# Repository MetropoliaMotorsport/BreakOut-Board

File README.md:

# BreakOut-Board
New BOB design

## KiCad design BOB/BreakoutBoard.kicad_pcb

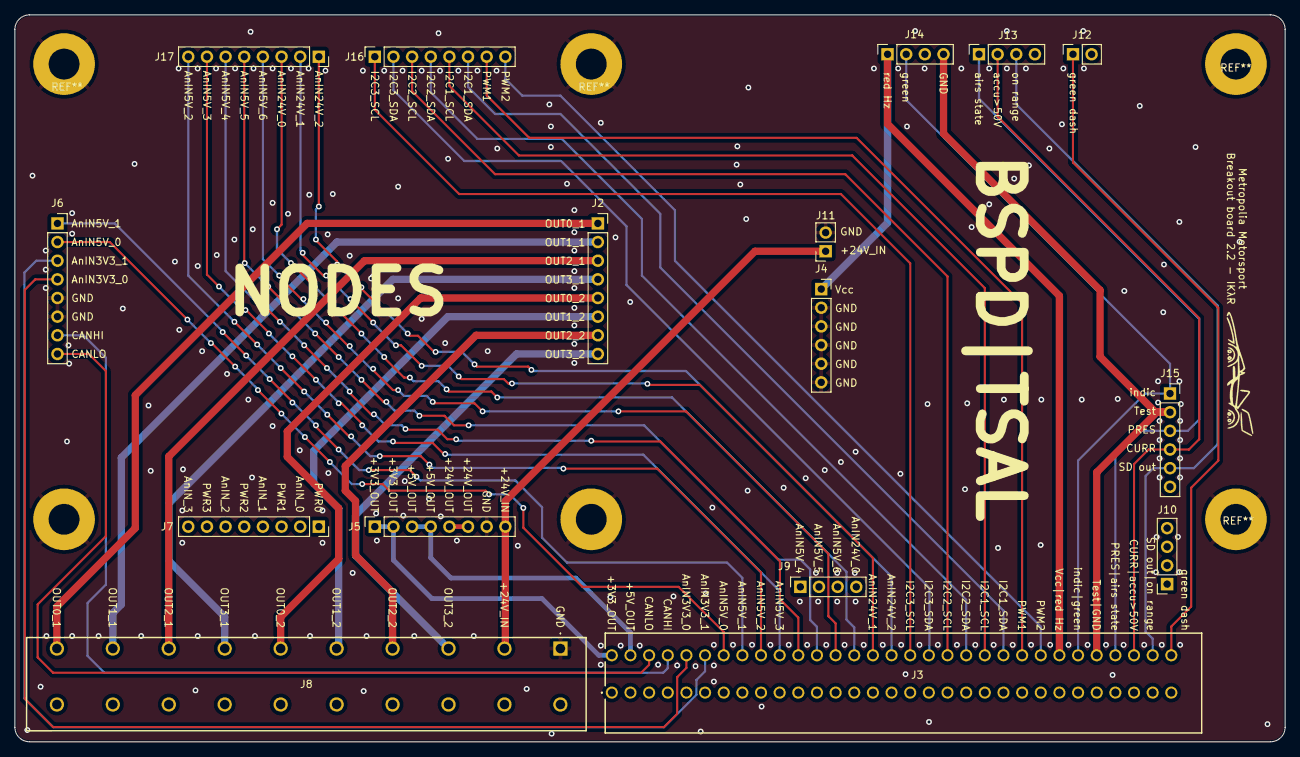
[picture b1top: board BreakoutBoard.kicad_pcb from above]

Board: 2 copper layers, 173.0 x 99.0 mm, 16 parts (0 on the bottom side), 42 nets.

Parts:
J2, J5, J6, J7, J16, J17: Conn_01x08; PinSocket_1x08_P2.54mm_Vertical
J3: 1706013; 35_con_Phoenix
J4, J15: Conn_01x06; PinSocket_1x06_P2.54mm_Vertical
J8: 1700884
J9, J10, J13, J14: Conn_01x04; PinSocket_1x04_P2.54mm_Vertical
J11, J12: Conn_01x02; PinSocket_1x02_P2.54mm_Vertical

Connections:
/+3V3_OUT: J3.2, J5.1, J5.2
/+5V_OUT: J3.4, J5.3, J5.4
/+24V_OUT: J5.5, J5.6
/AnIN3V3_0: J3.10, J6.4
/AnIN3V3_1: J3.12, J6.3
/AnIN5V_0: J3.14, J6.2
/AnIN5V_1: J3.16, J6.1
/AnIN5V_2: J3.18, J17.8
/AnIN5V_3: J3.20, J17.7
/AnIN5V_4: J3.22, J17.6
/AnIN5V_5: J3.24, J17.5
/AnIN5V_6: J3.26, J17.4
/AnIN24V_0: J3.28, J17.3
/AnIN24V_1: J3.30, J17.2
/AnIN24V_2: J3.32, J17.1
/CANHI: J3.8, J6.7
/CANLO: J3.6, J6.8
/CURR / accu>50V: J3.58, J13.2, J15.4
/GND: J4.2, J4.3, J4.4, J4.5, J4.6, J5.7, J6.5, J6.6, J8.1, J11.2
/I2C1_SCL: J3.42, J16.5
/I2C1_SDA: J3.44, J16.6
/I2C2_SCL: J3.38, J16.3
/I2C2_SDA: J3.40, J16.4
/I2C3_SCL: J3.34, J16.1
/I2C3_SDA: J3.36, J16.2
/OUT0_1: J2.1, J8.10
/OUT0_2: J2.5, J8.6
/OUT1_1: J2.2, J8.9
/OUT1_2: J2.6, J8.5
/OUT2_1: J2.3, J8.8
/OUT2_2: J2.7, J8.4
/OUT3_1: J2.4, J8.7
/OUT3_2: J2.8, J8.3
/PRES / airs state: J3.56, J13.1, J15.3
/PWM1: J3.46, J16.7
/PWM2: J3.48, J16.8
/SD out / on range: J3.60, J13.3, J15.5
/Test / GND: J3.54, J14.4, J15.2
/Vcc / red Hz: J3.50, J4.1, J14.1
/Vin: J5.8, J8.2, J11.1
/green dash: J3.62, J12.1
/indic / green: J3.52, J14.2, J15.1

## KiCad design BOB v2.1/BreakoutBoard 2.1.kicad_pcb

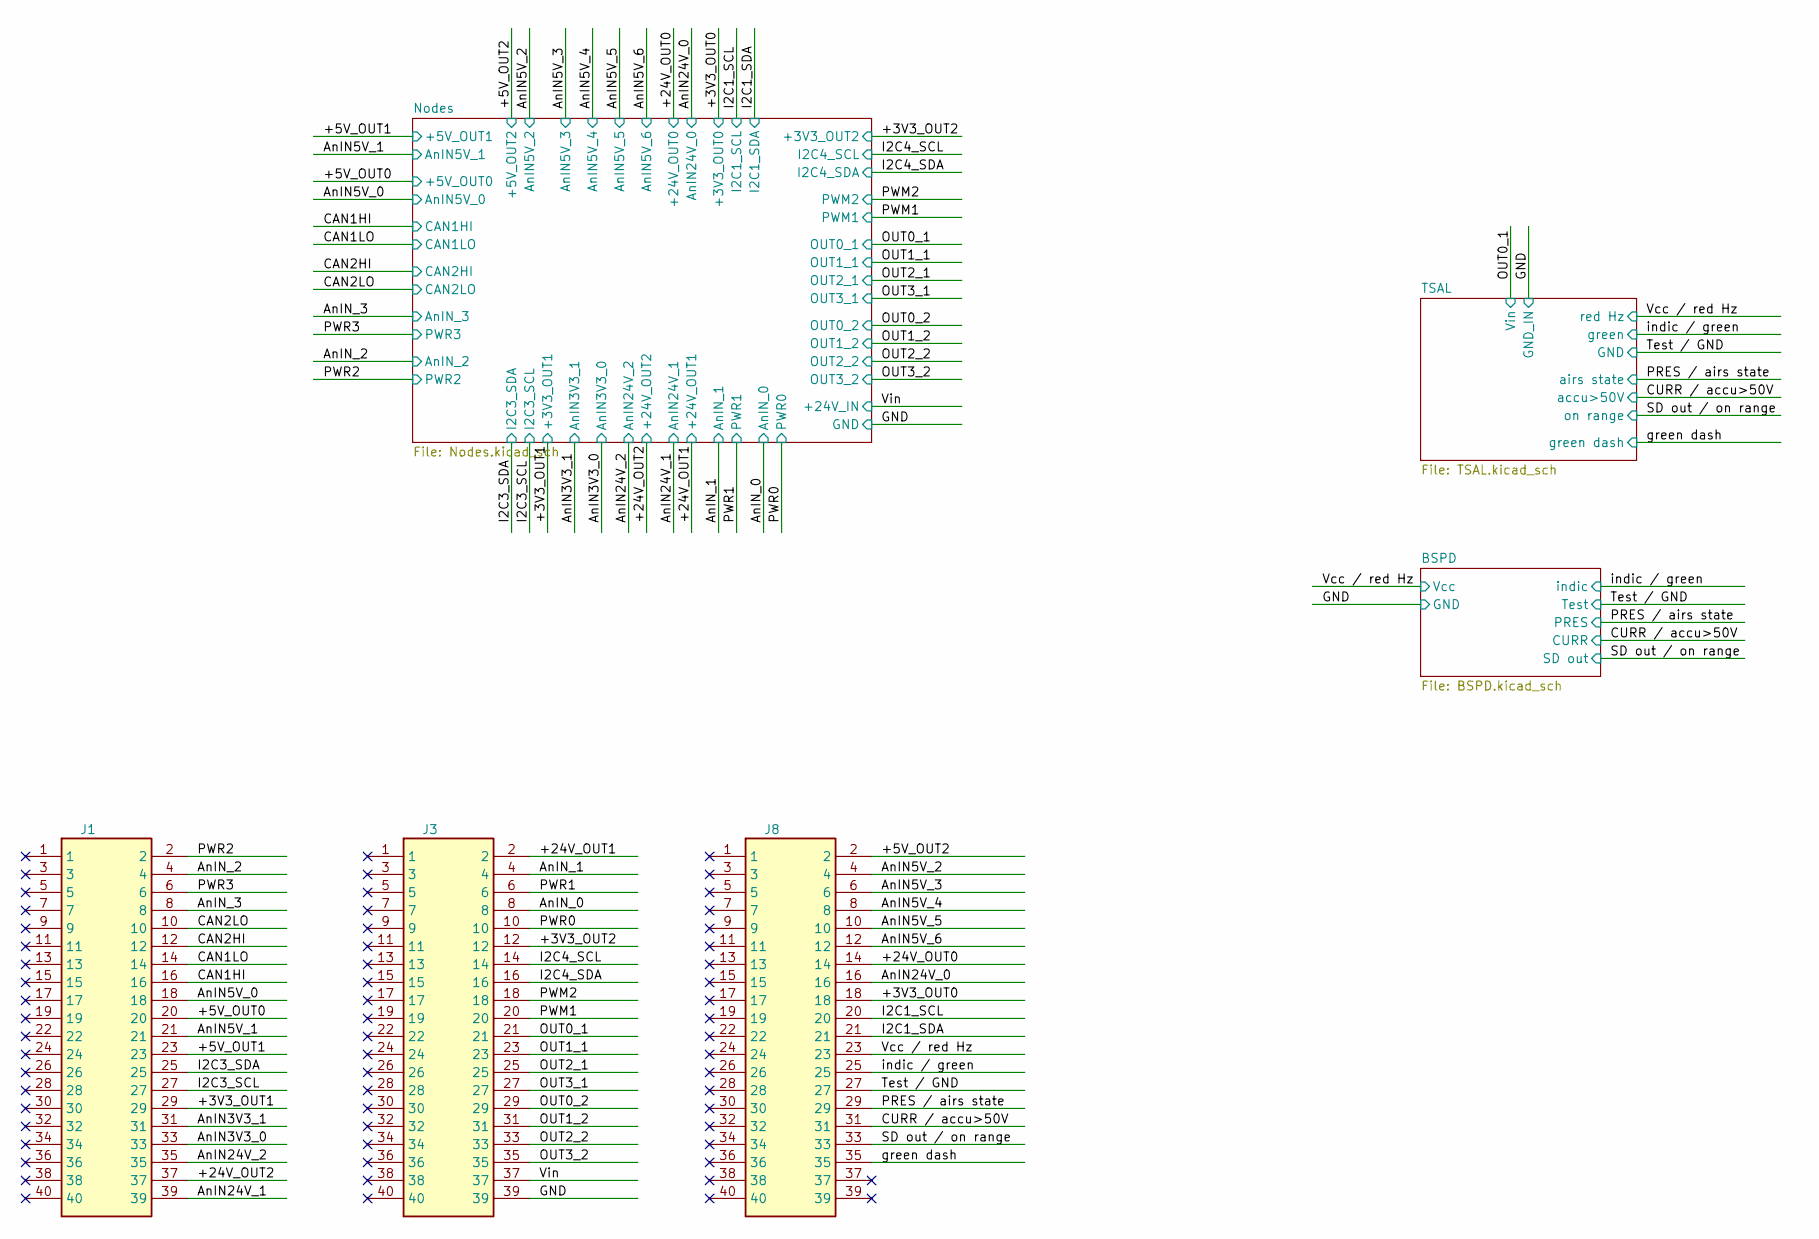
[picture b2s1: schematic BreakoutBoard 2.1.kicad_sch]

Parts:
J1, J3, J8: 1706013; Manufacturer_Part_Number 1706013; Mouser Part Number 651-1706013

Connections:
/+3V3_OUT0: J8.18; also elsewhere on the board
/+3V3_OUT1: J1.29; also elsewhere on the board
/+3V3_OUT2: J3.12; also elsewhere on the board
/+5V_OUT0: J1.20; also elsewhere on the board
/+5V_OUT1: J1.23; also elsewhere on the board
/+5V_OUT2: J8.2; also elsewhere on the board
/+24V_OUT0: J8.14; also elsewhere on the board
/+24V_OUT1: J3.2; also elsewhere on the board
/+24V_OUT2: J1.37; also elsewhere on the board
/AnIN3V3_0: J1.33; also elsewhere on the board
/AnIN3V3_1: J1.31; also elsewhere on the board
/AnIN5V_0: J1.18; also elsewhere on the board
/AnIN5V_1: J1.21; also elsewhere on the board
/AnIN5V_2: J8.4; also elsewhere on the board
/AnIN5V_3: J8.6; also elsewhere on the board
/AnIN5V_4: J8.8; also elsewhere on the board
/AnIN5V_5: J8.10; also elsewhere on the board
/AnIN5V_6: J8.12; also elsewhere on the board
/AnIN24V_0: J8.16; also elsewhere on the board
/AnIN24V_1: J1.39; also elsewhere on the board
/AnIN24V_2: J1.35; also elsewhere on the board
/AnIN_0: J3.8; also elsewhere on the board
/AnIN_1: J3.4; also elsewhere on the board
/AnIN_2: J1.4; also elsewhere on the board
/AnIN_3: J1.8; also elsewhere on the board
/CAN1HI: J1.16; also elsewhere on the board
/CAN1LO: J1.14; also elsewhere on the board
/CAN2HI: J1.12; also elsewhere on the board
/CAN2LO: J1.10; also elsewhere on the board
/CURR / accu>50V: J8.31; also elsewhere on the board
/GND: J3.39; also elsewhere on the board
/I2C1_SCL: J8.20; also elsewhere on the board
/I2C1_SDA: J8.21; also elsewhere on the board
/I2C3_SCL: J1.27; also elsewhere on the board
/I2C3_SDA: J1.25; also elsewhere on the board
/I2C4_SCL: J3.14; also elsewhere on the board
/I2C4_SDA: J3.16; also elsewhere on the board
/OUT0_1: J3.21; also elsewhere on the board
/OUT0_2: J3.29; also elsewhere on the board
/OUT1_1: J3.23; also elsewhere on the board
/OUT1_2: J3.31; also elsewhere on the board
/OUT2_1: J3.25; also elsewhere on the board
/OUT2_2: J3.33; also elsewhere on the board
/OUT3_1: J3.27; also elsewhere on the board
/OUT3_2: J3.35; also elsewhere on the board
/PRES / airs state: J8.29; also elsewhere on the board
/PWM1: J3.20; also elsewhere on the board
/PWM2: J3.18; also elsewhere on the board
/PWR0: J3.10; also elsewhere on the board
/PWR1: J3.6; also elsewhere on the board
/PWR2: J1.2; also elsewhere on the board
/PWR3: J1.6; also elsewhere on the board
/SD out / on range: J8.33; also elsewhere on the board
/Test / GND: J8.27; also elsewhere on the board
/Vcc / red Hz: J8.23; also elsewhere on the board
/Vin: J3.37; also elsewhere on the board
/green dash: J8.35; also elsewhere on the board
/indic / green: J8.25; also elsewhere on the board

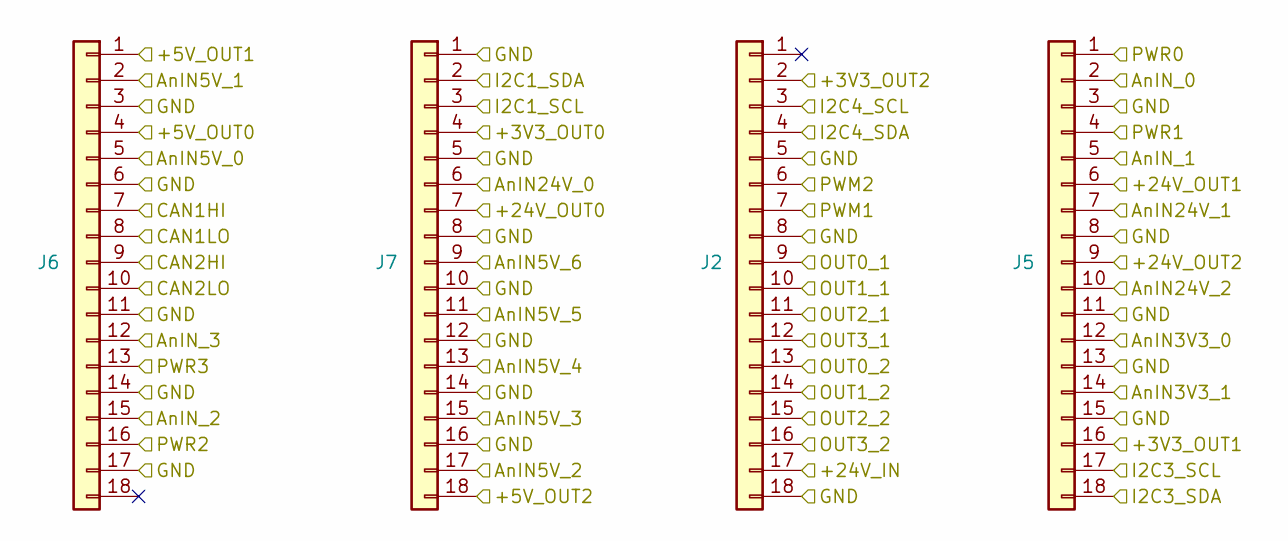
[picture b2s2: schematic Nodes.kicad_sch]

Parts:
J2, J5, J6, J7: Conn_01x18; PinSocket_1x18_P2.54mm_Vertical

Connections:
/+3V3_OUT0: J7.4; also elsewhere on the board
/+3V3_OUT1: J5.16; also elsewhere on the board
/+3V3_OUT2: J2.2; also elsewhere on the board
/+5V_OUT0: J6.4; also elsewhere on the board
/+5V_OUT1: J6.1; also elsewhere on the board
/+5V_OUT2: J7.18; also elsewhere on the board
/+24V_OUT0: J7.7; also elsewhere on the board
/+24V_OUT1: J5.6; also elsewhere on the board
/+24V_OUT2: J5.9; also elsewhere on the board
/AnIN3V3_0: J5.12; also elsewhere on the board
/AnIN3V3_1: J5.14; also elsewhere on the board
/AnIN5V_0: J6.5; also elsewhere on the board
/AnIN5V_1: J6.2; also elsewhere on the board
/AnIN5V_2: J7.17; also elsewhere on the board
/AnIN5V_3: J7.15; also elsewhere on the board
/AnIN5V_4: J7.13; also elsewhere on the board
/AnIN5V_5: J7.11; also elsewhere on the board
/AnIN5V_6: J7.9; also elsewhere on the board
/AnIN24V_0: J7.6; also elsewhere on the board
/AnIN24V_1: J5.7; also elsewhere on the board
/AnIN24V_2: J5.10; also elsewhere on the board
/AnIN_0: J5.2; also elsewhere on the board
/AnIN_1: J5.5; also elsewhere on the board
/AnIN_2: J6.15; also elsewhere on the board
/AnIN_3: J6.12; also elsewhere on the board
/CAN1HI: J6.7; also elsewhere on the board
/CAN1LO: J6.8; also elsewhere on the board
/CAN2HI: J6.9; also elsewhere on the board
/CAN2LO: J6.10; also elsewhere on the board
/GND: J2.5, J2.8, J2.18, J5.3, J5.8, J5.11, J5.13, J5.15, J6.3, J6.6, J6.11, J6.14, J6.17, J7.1, J7.5, J7.8, J7.10, J7.12, J7.14, J7.16; also elsewhere on the board
/I2C1_SCL: J7.3; also elsewhere on the board
/I2C1_SDA: J7.2; also elsewhere on the board
/I2C3_SCL: J5.17; also elsewhere on the board
/I2C3_SDA: J5.18; also elsewhere on the board
/I2C4_SCL: J2.3; also elsewhere on the board
/I2C4_SDA: J2.4; also elsewhere on the board
/OUT0_1: J2.9; also elsewhere on the board
/OUT0_2: J2.13; also elsewhere on the board
/OUT1_1: J2.10; also elsewhere on the board
/OUT1_2: J2.14; also elsewhere on the board
/OUT2_1: J2.11; also elsewhere on the board
/OUT2_2: J2.15; also elsewhere on the board
/OUT3_1: J2.12; also elsewhere on the board
/OUT3_2: J2.16; also elsewhere on the board
/PWM1: J2.7; also elsewhere on the board
/PWM2: J2.6; also elsewhere on the board
/PWR0: J5.1; also elsewhere on the board
/PWR1: J5.4; also elsewhere on the board
/PWR2: J6.16; also elsewhere on the board
/PWR3: J6.13; also elsewhere on the board
/Vin: J2.17; also elsewhere on the board

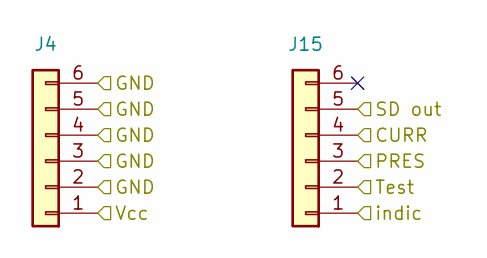
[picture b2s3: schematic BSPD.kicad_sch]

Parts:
J4, J15: Conn_01x06; PinSocket_1x06_P2.54mm_Vertical

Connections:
/CURR / accu>50V: J15.4; also elsewhere on the board
/GND: J4.2, J4.3, J4.4, J4.5, J4.6; also elsewhere on the board
/PRES / airs state: J15.3; also elsewhere on the board
/SD out / on range: J15.5; also elsewhere on the board
/Test / GND: J15.2; also elsewhere on the board
/Vcc / red Hz: J4.1; also elsewhere on the board
/indic / green: J15.1; also elsewhere on the board

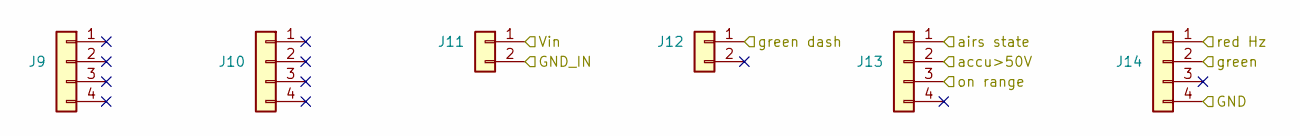
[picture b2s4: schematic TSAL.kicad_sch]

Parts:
J9, J10, J13, J14: Conn_01x04; PinSocket_1x04_P2.54mm_Vertical
J11, J12: Conn_01x02; PinSocket_1x02_P2.54mm_Vertical

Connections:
/CURR / accu>50V: J13.2; also elsewhere on the board
/GND: J11.2; also elsewhere on the board
/OUT0_1: J11.1; also elsewhere on the board
/PRES / airs state: J13.1; also elsewhere on the board
/SD out / on range: J13.3; also elsewhere on the board
/Test / GND: J14.4; also elsewhere on the board
/Vcc / red Hz: J14.1; also elsewhere on the board
/green dash: J12.1; also elsewhere on the board
/indic / green: J14.2; also elsewhere on the board

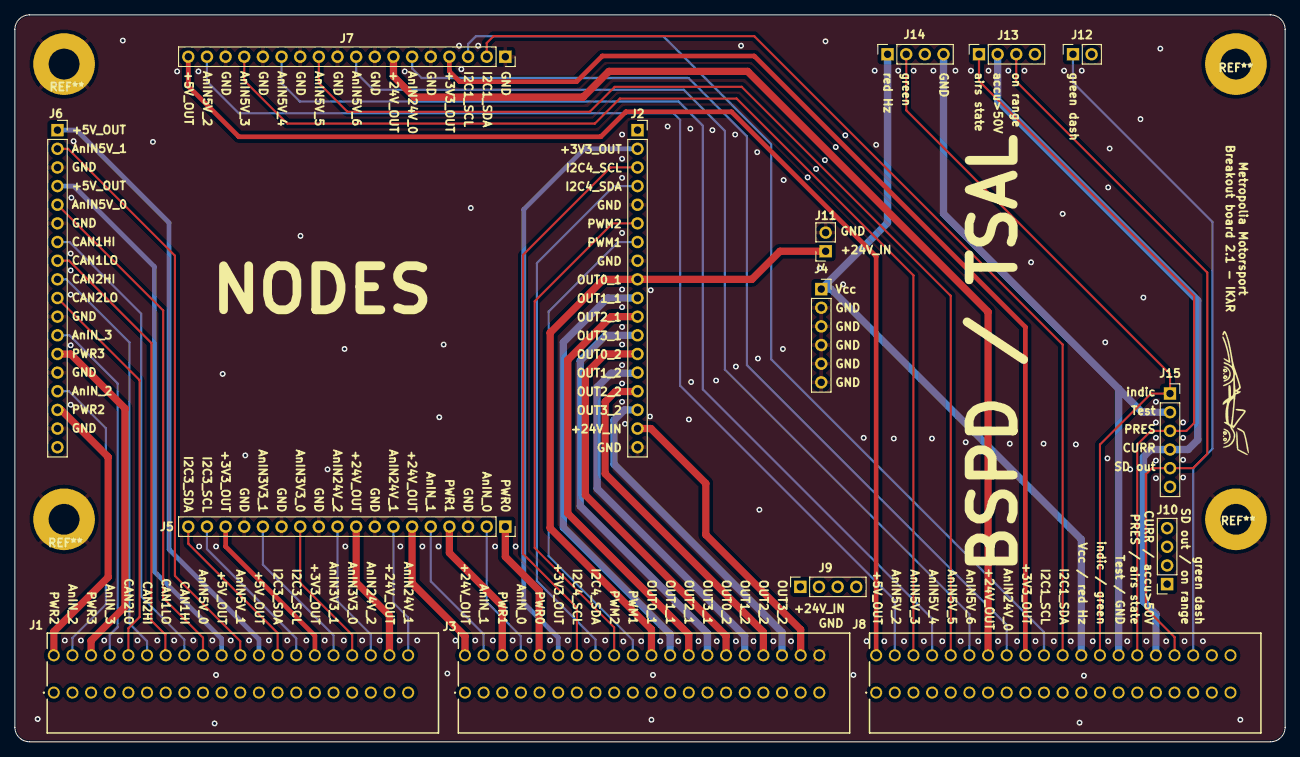
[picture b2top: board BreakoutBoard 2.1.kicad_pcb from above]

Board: 2 copper layers, 173.0 x 99.0 mm, 15 parts (0 on the bottom side), 58 nets.

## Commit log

2024-06-08 BOB v2.1
2024-06-18 BOB v2.1.2
    - Reduced font size
    - Fixed mistake with CAN numbers
2024-06-22 BOB v2.2
    - New connector for OUT signals and input power pins (Connection for filter modules is not available on this version due to the size of connectors and maximum length of the board)
    - Added two big holes for better and more stable connection in the car
    - New layout and support for Nodes v2.2
    - Created a combined design of 2.54mm connector for more efficient area usage
    - PDF schematic added
    - Other small visual changes
2024-07-02 v2.2.1
    -TSAL now connected to +24V_IN instead of OUT0_1
2024-07-02 v2.2.3
    - New layout
    - Removed from connectors:
    * 2x +24V_OUT
    * 1x +3V3_OUT
    * 1x +5V_OUT
